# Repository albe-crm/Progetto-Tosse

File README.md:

# Progetto-Tosse
progetto lab poli

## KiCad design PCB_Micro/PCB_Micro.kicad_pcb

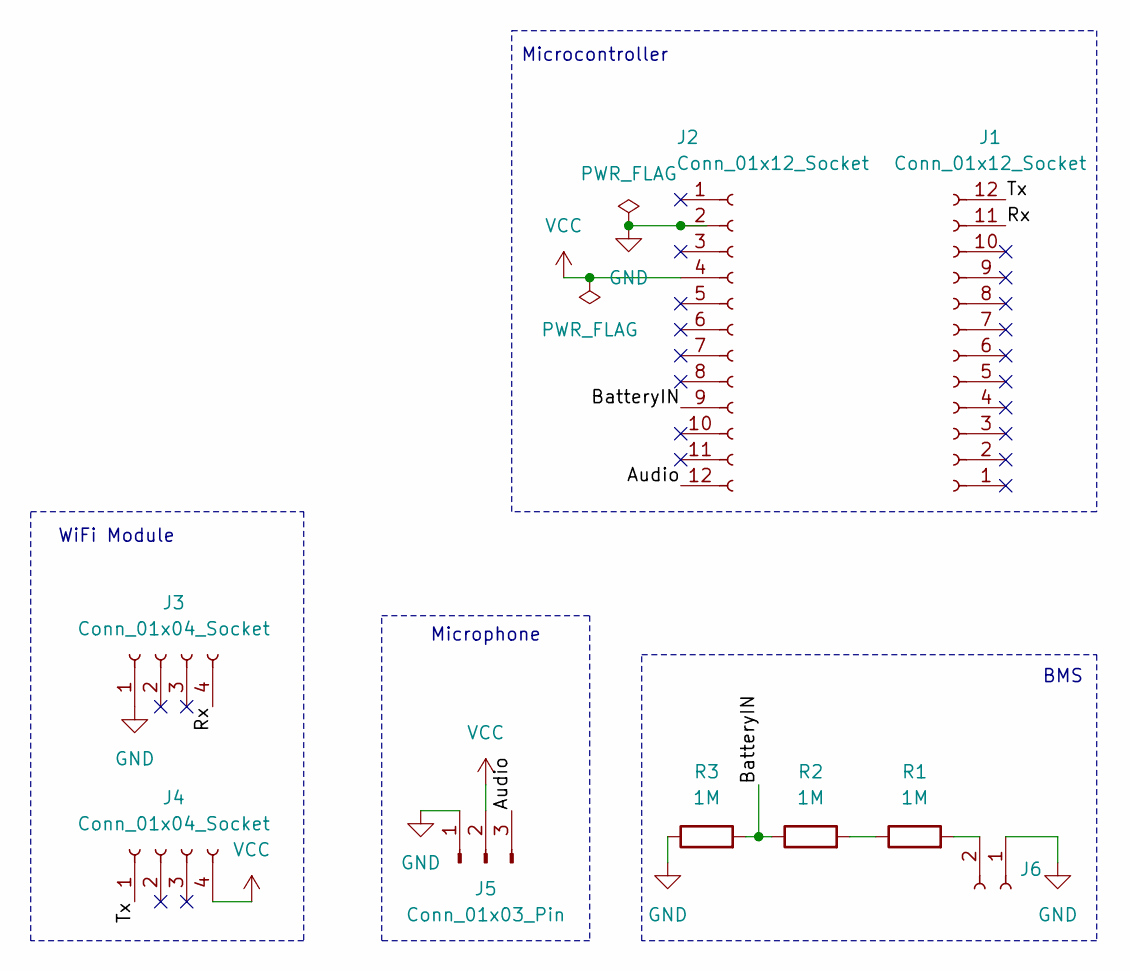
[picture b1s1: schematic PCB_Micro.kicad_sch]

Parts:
J1, J2: Conn_01x12_Socket; PinHeader_1x12_P2.54mm_Vertical
J3, J4: Conn_01x04_Socket; PinSocket_1x04_P2.54mm_Vertical
J5: Conn_01x03_Pin; JST_XA_B03B-XASK-1_1x03_P2.50mm_Vertical
J6: Conn_01x02_Socket; JST_XH_B2B-XH-AM_1x02_P2.50mm_Vertical
R1, R2, R3: 1M; R_2512_6332Metric_Pad1.40x3.35mm_HandSolder

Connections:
/Audio: J2.12, J5.3
/BatteryIN: J2.9, R2.1, R3.2
/Rx: J1.11, J3.4
/Tx: J1.12, J4.1
GND: J2.2, J3.1, J5.1, J6.1, R3.1
unnamed: J6.2, R1.2
unnamed: R1.1, R2.2
VCC: J2.4, J4.4, J5.2

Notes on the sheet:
WiFi Module
BMS
Microcontroller
Microphone

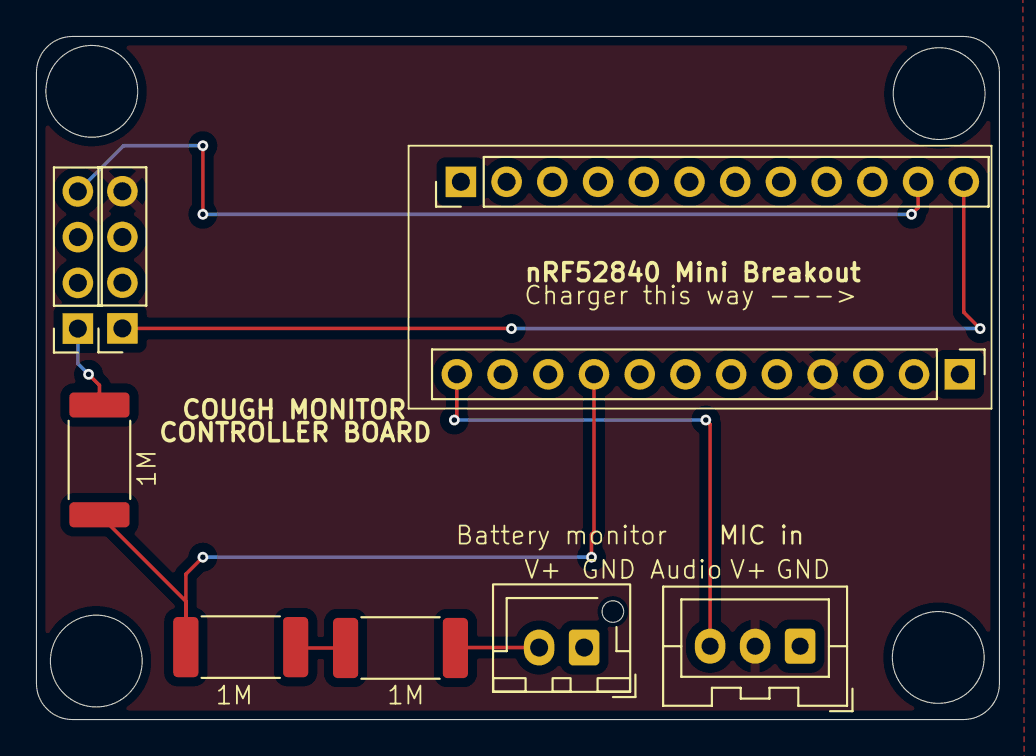
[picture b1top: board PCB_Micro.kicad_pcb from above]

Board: 2 copper layers, 53.5 x 37.9 mm, 9 parts (0 on the bottom side), 8 nets.

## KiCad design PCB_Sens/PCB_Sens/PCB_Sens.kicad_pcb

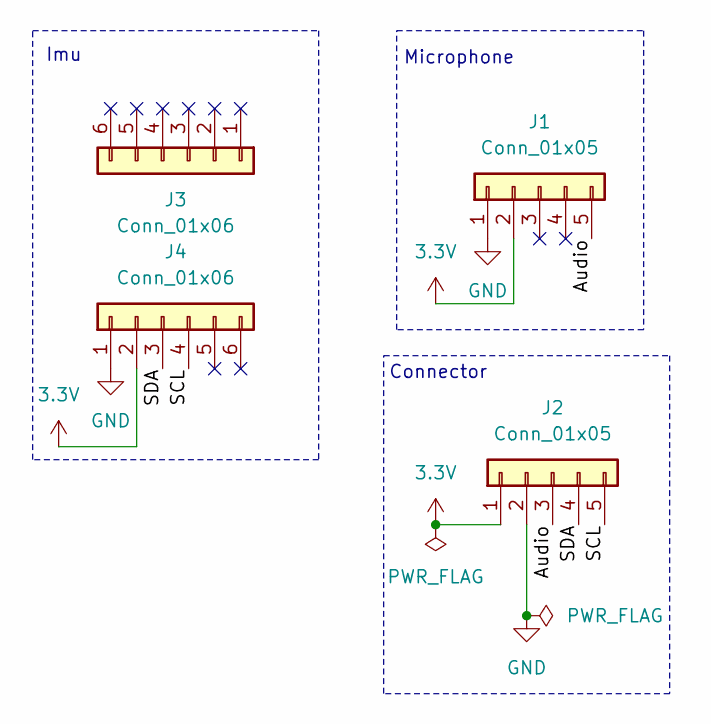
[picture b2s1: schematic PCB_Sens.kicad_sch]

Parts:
J1: Conn_01x05; PinSocket_1x05_P2.54mm_Vertical
J2: Conn_01x05; JST_XA_B05B-XASK-1-A_1x05_P2.50mm_Vertical
J3, J4: Conn_01x06; PinSocket_1x06_P2.54mm_Vertical

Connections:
3.3V: J1.2, J2.1, J4.2
/Audio: J1.5, J2.3
/SCL: J2.5, J4.4
/SDA: J2.4, J4.3
GND: J1.1, J2.2, J4.1

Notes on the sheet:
Imu
Microphone
Connector

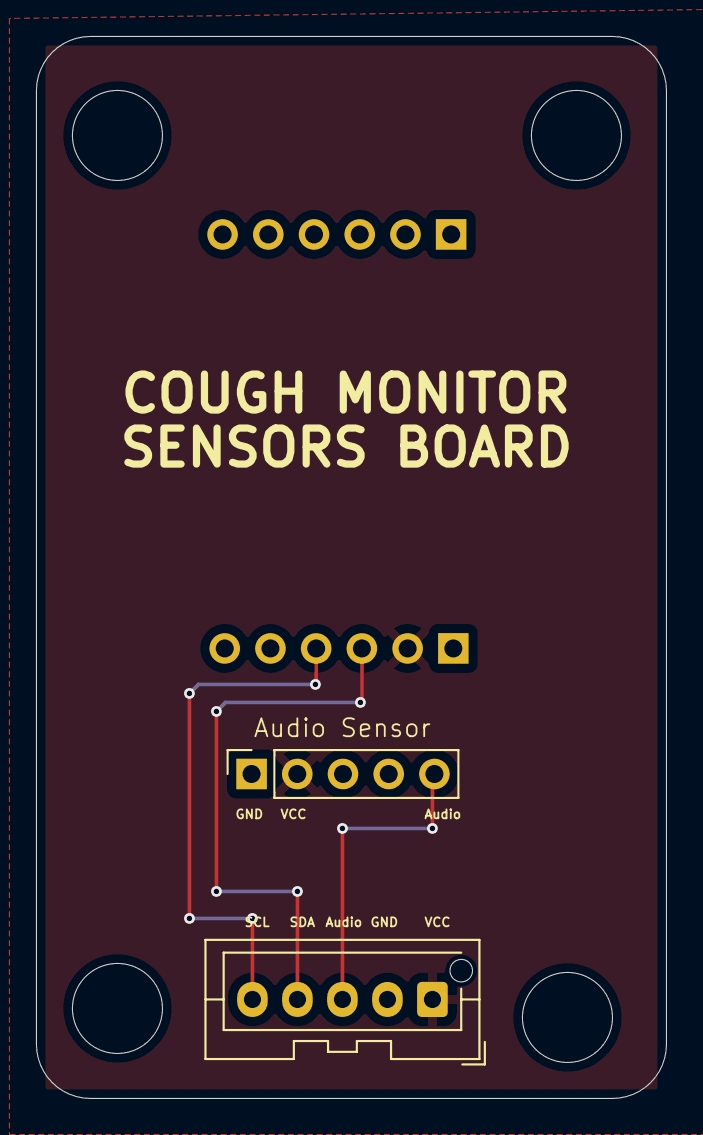
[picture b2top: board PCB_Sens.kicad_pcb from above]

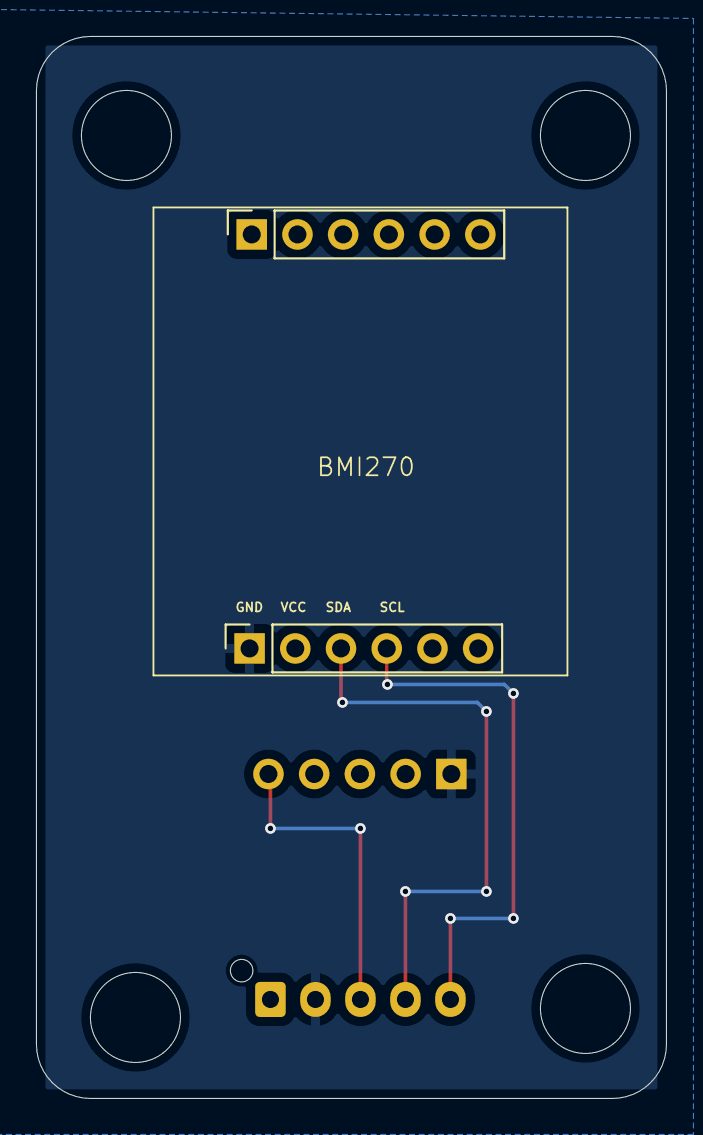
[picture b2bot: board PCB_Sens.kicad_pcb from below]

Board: 2 copper layers, 35.0 x 59.0 mm, 4 parts (2 on the bottom side), 5 nets.

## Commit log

2025-10-09 filtraggio microfono
2025-10-22 Add files via upload
    codice arduino per il microfono che rileva la presenza di tosse o meno unendo zero crossing rate e valutazioni sull'energia del segnale
2025-10-22 codice per l'IMU
2025-10-22 codice microfono con aggiunta del guadagno
2025-11-16 codice sensor fusion (parametri da calibrare)
2025-11-19 Create Completo_WiFi.ino
    Added firmware with WiFi
2025-11-30 aggiornato per plottare integrale tosse
2025-12-03 messaggi di debug per sensor fusion
2025-12-03 codice arduino per acquisizione per calibrazione
2025-12-03 codice matlab per acquisire il dataset per la calibrazione
2025-12-10 codice per acquisire dati calibrazione
2025-12-10 codice matlab per validare le soglie
2026-02-04 Added PCB, Webapp and Firmware
2026-02-08 file calibrazione finale
2026-02-09 Messa a posto e file matlab
2026-02-15 Added demo fix for battery
